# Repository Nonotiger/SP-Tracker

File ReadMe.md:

This project is about a Solar Panel which tracks the sun. The main focus for the project electrically, is the development of the BMS, and charger for the batteries. Code wise the main focus is the control of stepper motors, and the development of an algorithm for solar tracking based on energy output. Mechanically the focus is to develop stepper motor gears that can bear heavy loads, and to build a structure that can withstand Danish weather conditions.

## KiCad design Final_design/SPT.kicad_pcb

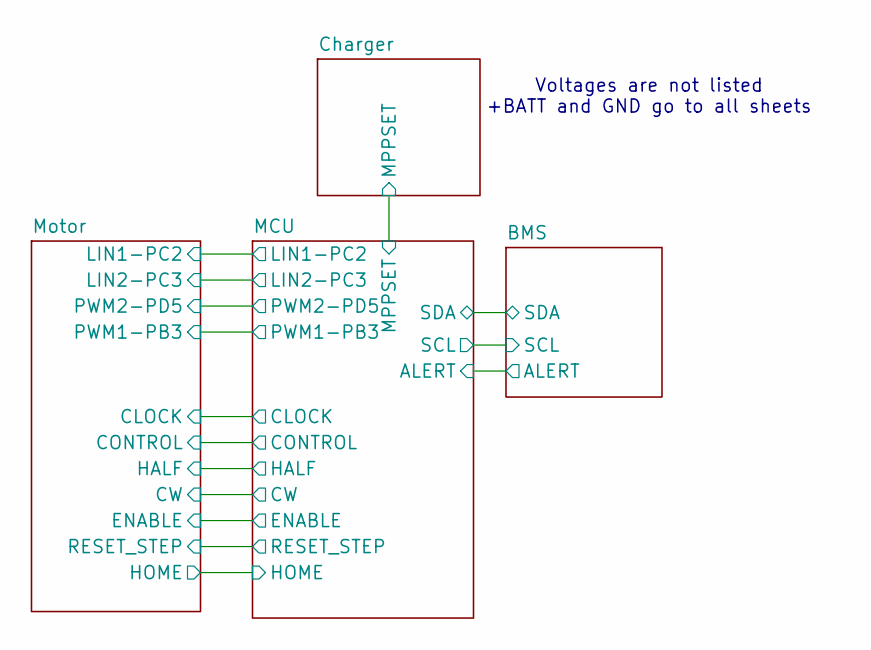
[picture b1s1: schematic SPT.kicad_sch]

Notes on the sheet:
Voltages are not listed +BATT and GND go to all sheets

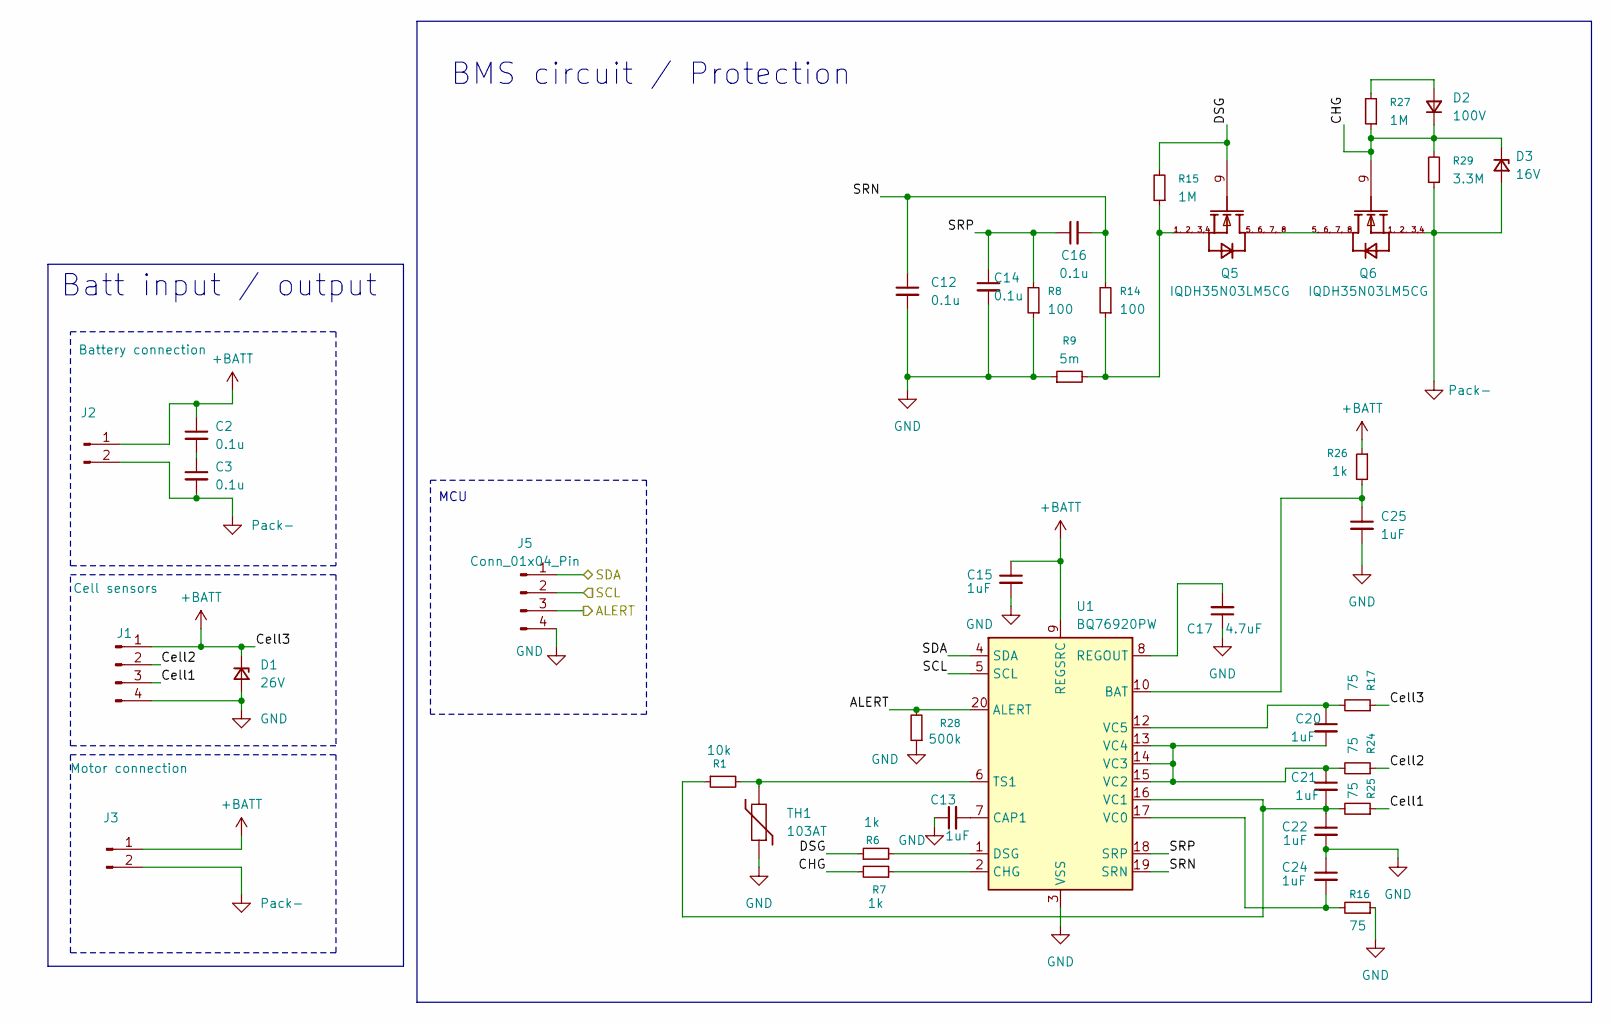
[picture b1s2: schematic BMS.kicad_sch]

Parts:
C2, C3, C12, C14, C16: 0.1u; C_0805_2012Metric_Pad1.18x1.45mm_HandSolder
C13, C15, C20, C21, C22, C24, C25: 1uF; C_0805_2012Metric_Pad1.18x1.45mm_HandSolder
C17: 4.7uF; C_0805_2012Metric_Pad1.18x1.45mm_HandSolder
D1: 26V; D_SOD-123
D2: 100V; D_SOD-123
D3: 16V; D_SOD-123
J1: Cell sensors; PinHeader_1x04_P2.54mm_Vertical
J2: Battery connection; TerminalBlock_Phoenix_MKDS-1,5-2_1x02_P5.00mm_Horizontal
J3: Motor connection; TerminalBlock_Phoenix_MKDS-1,5-2_1x02_P5.00mm_Horizontal
J5: Conn_01x04_Pin; PinHeader_1x04_P2.54mm_Vertical
Q5, Q6: IQDH35N03LM5CG; IFX-PG-TTFN-9-2-V
R1: 10k; R_0805_2012Metric_Pad1.20x1.40mm_HandSolder
R6, R7, R26: 1k; R_0805_2012Metric_Pad1.20x1.40mm_HandSolder
R8, R14: 100; R_0805_2012Metric_Pad1.20x1.40mm_HandSolder
R9: 5m; R_2512_6332Metric_Pad1.40x3.35mm_HandSolder
R15, R27: 1M; R_0805_2012Metric_Pad1.20x1.40mm_HandSolder
R16, R17, R24, R25: 75; R_0805_2012Metric_Pad1.20x1.40mm_HandSolder
R28: 500k; R_0805_2012Metric_Pad1.20x1.40mm_HandSolder
R29: 3.3M; R_0805_2012Metric_Pad1.20x1.40mm_HandSolder
TH1: 103AT; R_0603_1608Metric_Pad0.98x0.95mm_HandSolder
U1: BQ76920PW; TSSOP-20_4.4x6.5mm_P0.65mm

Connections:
+BATT: C2.1, C15.1, D1.1 (K), J1.1, J2.1, J3.1, R17.1, R26.1, U1.9 (REGSRC); also elsewhere on the board
/BMS/ALERT: J5.3, R28.2, U1.20 (ALERT); also elsewhere on the board
/BMS/CHG: D2.1 (K), D3.1 (K), Q6.9 (GATE), R7.2, R27.1, R29.2
/BMS/Cell1: J1.3, R25.1
/BMS/Cell2: J1.2, R24.1
/BMS/DSG: Q5.9 (GATE), R6.1, R15.2
/BMS/SCL: J5.2, U1.5 (SCL); also elsewhere on the board
/BMS/SDA: J5.1, U1.4 (SDA); also elsewhere on the board
/BMS/SRN: C12.1, C16.2, R14.2, U1.19 (SRN)
/BMS/SRP: C14.1, C16.1, R8.2, U1.18 (SRP)
GND: C12.2, C13.1, C14.2, C15.2, C17.1, C22.2, C24.1, C25.2, D1.2 (A), J1.4, J5.4, R8.1, R9.1, R16.1, R28.1, TH1.1, U1.3 (VSS); also elsewhere on the board
unnamed: C2.2, C3.1
unnamed: D2.2 (A), R27.2
unnamed: Q5.1 (SOURCE1), Q5.2 (SOURCE2), Q5.3 (SOURCE3), Q5.4 (SOURCE4), R9.2, R14.1, R15.1
unnamed: C25.1, R26.2, U1.10 (BAT)
unnamed: C13.2, U1.7 (CAP1)
unnamed: R7.1, U1.2 (CHG)
unnamed: R6.2, U1.1 (DSG)
unnamed: C17.2, U1.8 (REGOUT)
unnamed: R1.2, TH1.2, U1.6 (TS1)
unnamed: C24.2, R16.2, U1.17 (VC0)
unnamed: C21.2, C22.1, R1.1, R25.2, U1.16 (VC1)
unnamed: C20.2, C21.1, R24.2, U1.13 (VC4), U1.14 (VC3), U1.15 (VC2)
unnamed: C20.1, R17.2, U1.12 (VC5)
Pack-: C3.2, D3.2 (A), J2.2, J3.2, Q6.1 (SOURCE1), Q6.2 (SOURCE2), Q6.3 (SOURCE3), Q6.4 (SOURCE4), R29.1; also elsewhere on the board

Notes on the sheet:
Batt input / output
BMS circuit / Protection
MCU

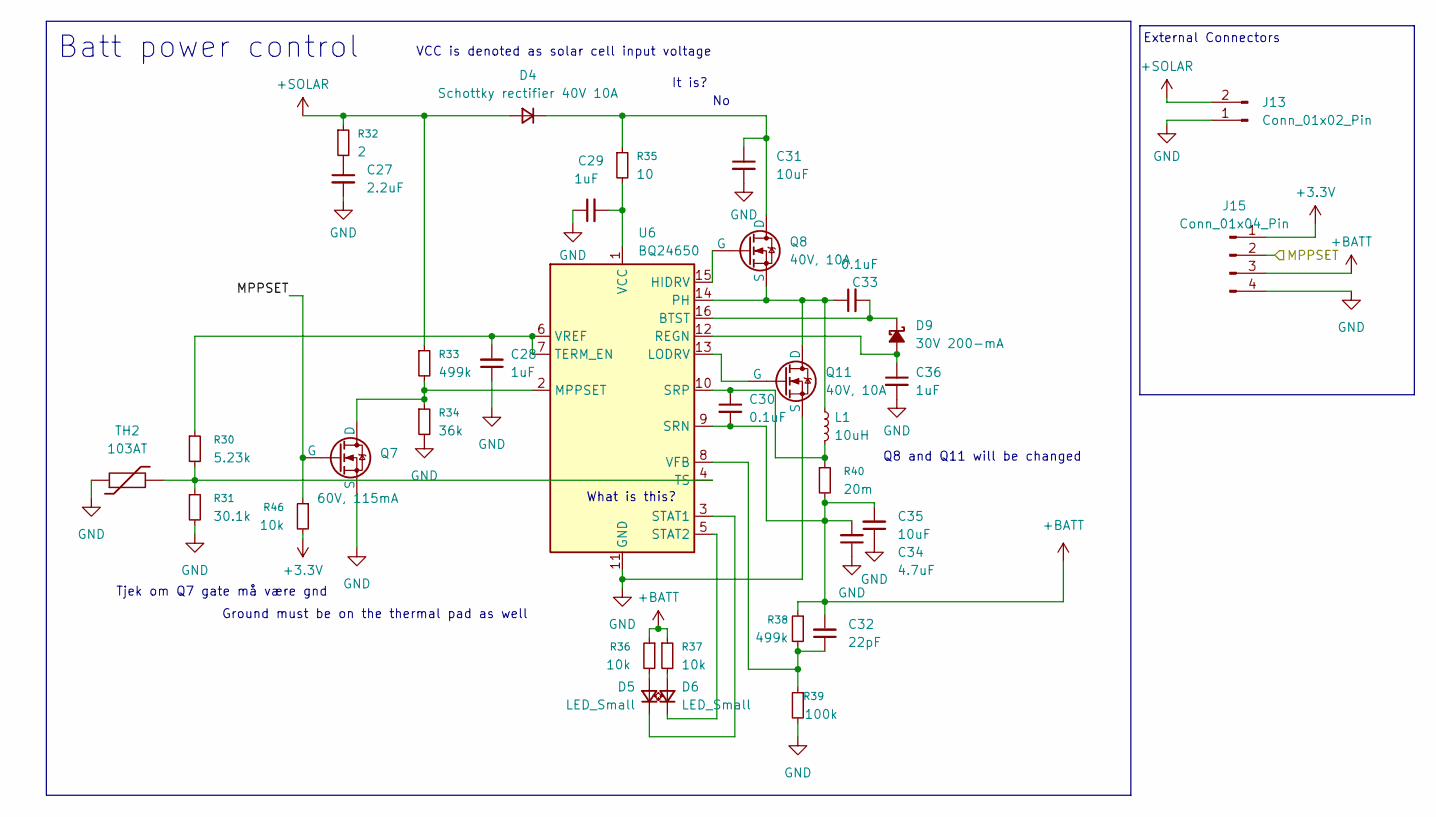
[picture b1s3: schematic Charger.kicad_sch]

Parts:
C27: 2.2uF; C_1210_3225Metric_Pad1.33x2.70mm_HandSolder
C28, C29, C36: 1uF; C_0805_2012Metric_Pad1.18x1.45mm_HandSolder
C30, C33: 0.1uF; C_0805_2012Metric_Pad1.18x1.45mm_HandSolder
C31, C35: 10uF; C_1210_3225Metric_Pad1.33x2.70mm_HandSolder
C32: 22pF; C_0805_2012Metric_Pad1.18x1.45mm_HandSolder
C34: 4.7uF; C_1210_3225Metric_Pad1.33x2.70mm_HandSolder
D4: Schottky rectifier 40V 10A; D_PowerDI-5
D5, D6: LED_Small; LED_0805_2012Metric_Pad1.15x1.40mm_HandSolder
D9: 30V 200-mA; SOT-23_Handsoldering
J13: Conn_01x02_Pin; TerminalBlock_Phoenix_MKDS-1,5-2_1x02_P5.00mm_Horizontal
J15: Conn_01x04_Pin; PinHeader_1x04_P2.54mm_Vertical
L1: 10uH; L_Vishay_IHLP-2525
Q7: 60V, 115mA; TO-220-3_Vertical
Q8, Q11: 40V, 10A; TO-220-3_Vertical
R30: 5.23k; R_0805_2012Metric_Pad1.20x1.40mm_HandSolder
R31: 30.1k; R_0805_2012Metric_Pad1.20x1.40mm_HandSolder
R32: 2; R_0805_2012Metric_Pad1.20x1.40mm_HandSolder
R33, R38: 499k; R_0805_2012Metric_Pad1.20x1.40mm_HandSolder
R34: 36k; R_0805_2012Metric_Pad1.20x1.40mm_HandSolder
R35: 10; R_0805_2012Metric_Pad1.20x1.40mm_HandSolder
R36, R37, R46: 10k; R_0805_2012Metric_Pad1.20x1.40mm_HandSolder
R39: 100k; R_0805_2012Metric_Pad1.20x1.40mm_HandSolder
R40: 20m; R_1206_3216Metric_Pad1.30x1.75mm_HandSolder
TH2: 103AT; R_0603_1608Metric_Pad0.98x0.95mm_HandSolder
U6: BQ24650; Texas_RVA_VQFN-16-1EP_3.5x3.5mm_P0.5mm_EP2.14x2.14mm_Therma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

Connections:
+3.3V: J15.1, R46.2; also elsewhere on the board
+BATT: C30.2, C32.2, C34.2, C35.2, J15.3, R36.1, R37.1, R38.1, R40.2, U6.9 (SRN); also elsewhere on the board
+SOLAR: D4.2 (A), J13.2, R32.1, R33.1
/Charger/MPPSET: J15.2, Q7.2 (G), R46.1; also elsewhere on the board
GND: C27.2, C28.1, C29.1, C31.2, C34.1, C35.1, C36.2, J13.1, J15.4, Q7.3 (S), Q11.3 (S), R31.2, R34.2, R39.2, TH2.1, U6.11 (GND), U6.17 (GND); also elsewhere on the board
unnamed: C27.1, R32.2
unnamed: C31.1, D4.1 (K), Q8.1 (D), R35.1
unnamed: D5.2 (A), R36.2
unnamed: D5.1 (K), U6.3 (STAT1)
unnamed: D6.2 (A), R37.2
unnamed: D6.1 (K), U6.5 (STAT2)
unnamed: C36.1, D9.2 (A), U6.12 (REGN)
unnamed: C33.2, D9.1 (K), U6.16 (BTST)
unnamed: Q7.1 (D), R33.2, R34.1, U6.2 (MPPSET)
unnamed: Q8.2 (G), U6.15 (HIDRV)
unnamed: C33.1, L1.1, Q8.3 (S), Q11.1 (D), U6.14 (PH)
unnamed: Q11.2 (G), U6.13 (LODRV)
unnamed: C30.1, L1.2, R40.1, U6.10 (SRP)
unnamed: C28.2, R30.1, U6.6 (VREF), U6.7 (TERM_EN)
unnamed: R30.2, R31.1, TH2.2, U6.4 (TS)
unnamed: C29.2, R35.2, U6.1 (VCC)
unnamed: C32.1, R38.2, R39.1, U6.8 (VFB)

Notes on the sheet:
Ground must be on the thermal pad as well
What is this?
External Connectors
Q8 and Q11 will be changed
VCC is denoted as solar cell input voltage
Tjek om Q7 gate må være gnd
Batt power control
It is?

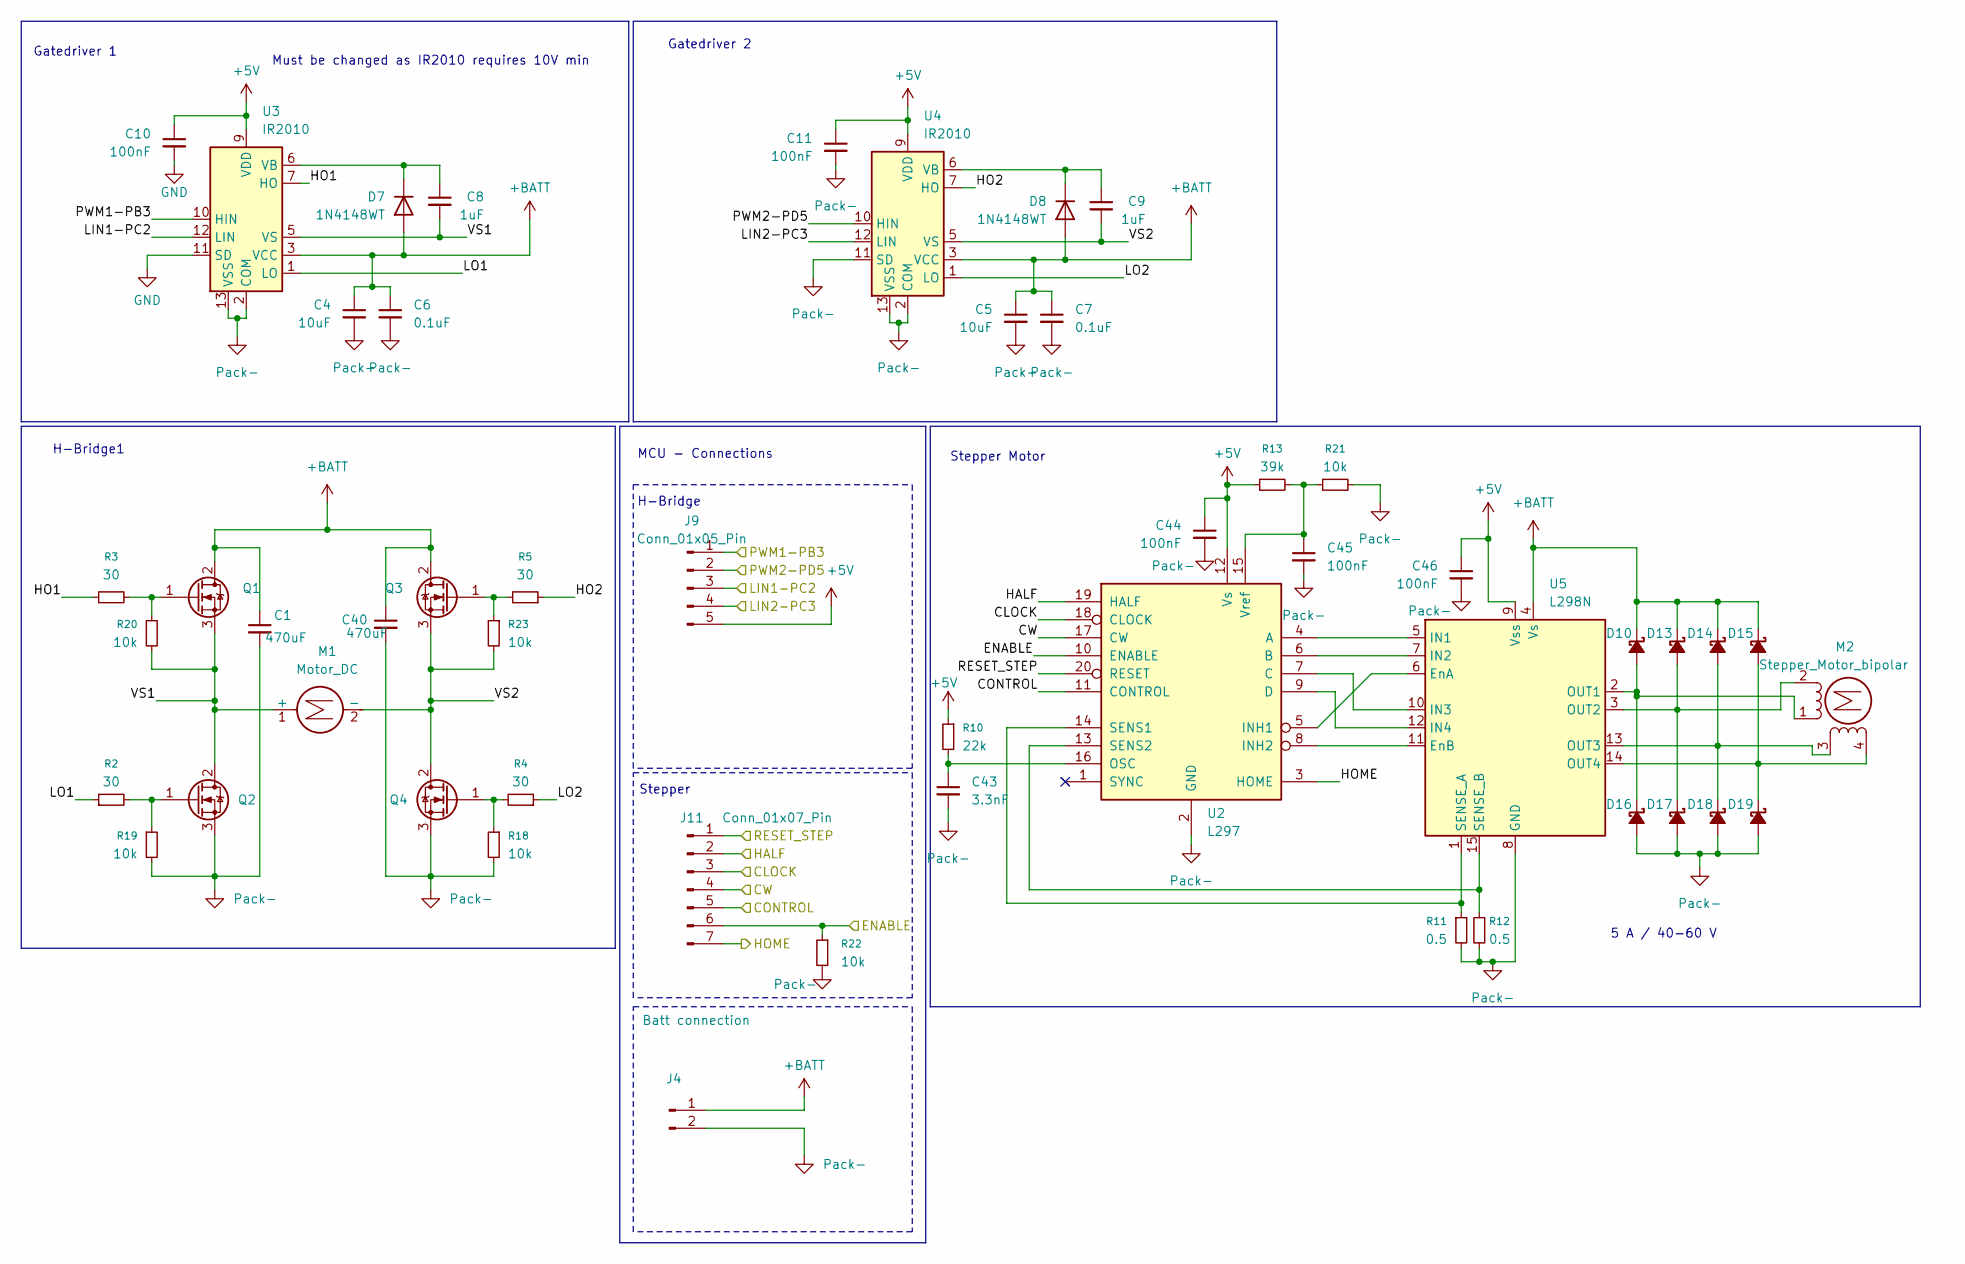
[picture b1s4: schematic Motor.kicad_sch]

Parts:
C1, C40: 470uF; CP_Radial_D12.5mm_P5.00mm
C4, C5: 10uF; C_1210_3225Metric_Pad1.33x2.70mm_HandSolder
C6, C7: 0.1uF; C_0805_2012Metric_Pad1.18x1.45mm_HandSolder
C8, C9: 1uF; C_0805_2012Metric_Pad1.18x1.45mm_HandSolder
C10, C11, C44, C45, C46: 100nF; C_0805_2012Metric_Pad1.18x1.45mm_HandSolder
C43: 3.3nF; C_0805_2012Metric_Pad1.18x1.45mm_HandSolder
D7, D8: 1N4148WT; D_SOD-523
D10, D13, D14, D15, D16, D17, D18, D19: D_Schottky_Small_Filled; D_SMA_Handsoldering
J4: Batt connection; TerminalBlock_Phoenix_MKDS-1,5-2_1x02_P5.00mm_Horizontal
J9: Conn_01x05_Pin; PinSocket_1x05_P2.54mm_Vertical
J11: Conn_01x07_Pin; PinHeader_1x07_P2.54mm_Vertical
M1: Motor_DC; TerminalBlock_Phoenix_MKDS-1,5-2_1x02_P5.00mm_Horizontal
M2: Stepper_Motor_bipolar; TerminalBlock_Phoenix_MKDS-1,5-4_1x04_P5.00mm_Horizontal
Q1, Q2, Q3, Q4: IRLZ34N; TO-220-3_Vertical
R2, R3, R4, R5: 30; R_0805_2012Metric_Pad1.20x1.40mm_HandSolder
R10: 22k; R_0805_2012Metric_Pad1.20x1.40mm_HandSolder
R11, R12: 0.5; R_0805_2012Metric_Pad1.20x1.40mm_HandSolder
R13: 39k; R_0805_2012Metric_Pad1.20x1.40mm_HandSolder
R18, R19, R20, R21, R22, R23: 10k; R_0805_2012Metric_Pad1.20x1.40mm_HandSolder
U2: L297; CERDIP-20_W7.62mm_SideBrazed
U3, U4: IR2010; DIP-14_W7.62mm
U5: L298N; TO-220-15_P2.54x5.08mm_StaggerOdd_Lead4.58mm_Vertical

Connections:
+5V: C10.1, C11.1, C44.1, C46.1, J9.5, R10.1, R13.1, U2.12 (Vs), U3.9 (VDD), U4.9 (VDD), U5.9 (Vss); also elsewhere on the board
+BATT: C1.1, C4.1, C5.1, C6.1, C7.1, C40.1, D7.2 (A), D8.2 (A), D10.1 (K), D13.1 (K), D14.1 (K), D15.1 (K), J4.1, Q1.2 (D), Q3.2 (D), U3.3 (VCC), U4.3 (VCC), U5.4 (Vs); also elsewhere on the board
/MCU/CLOCK: J11.3, U2.18 (CLOCK); also elsewhere on the board
/MCU/CONTROL: J11.5, U2.11 (CONTROL); also elsewhere on the board
/MCU/CW: J11.4, U2.17 (CW); also elsewhere on the board
/MCU/ENABLE: J11.6, R22.1, U2.10 (ENABLE); also elsewhere on the board
/MCU/HALF: J11.2, U2.19 (HALF); also elsewhere on the board
/MCU/HOME: J11.7, U2.3 (HOME); also elsewhere on the board
/MCU/LIN1-PC2: J9.3, U3.12 (LIN); also elsewhere on the board
/MCU/LIN2-PC3: J9.4, U4.12 (LIN); also elsewhere on the board
/MCU/PWM1-PB3: J9.1, U3.10 (HIN); also elsewhere on the board
/MCU/PWM2-PD5: J9.2, U4.10 (HIN); also elsewhere on the board
/MCU/RESET_STEP: J11.1, U2.20 (RESET); also elsewhere on the board
/Motor/HO1: R3.1, U3.7 (HO)
/Motor/HO2: R5.1, U4.7 (HO)
/Motor/LO1: R2.1, U3.1 (LO)
/Motor/LO2: R4.1, U4.1 (LO)
/Motor/VS1: C8.2, M1.1 (+), Q1.3 (S), Q2.2 (D), R20.2, U3.5 (VS)
/Motor/VS2: C9.2, M1.2 (-), Q3.3 (S), Q4.2 (D), R23.2, U4.5 (VS)
GND: C10.2, U3.11 (SD); also elsewhere on the board
unnamed: C8.1, D7.1 (K), U3.6 (VB)
unnamed: C9.1, D8.1 (K), U4.6 (VB)
unnamed: D10.2 (A), D16.1 (K), M2.1, U5.2 (OUT1)
unnamed: D13.2 (A), D17.1 (K), M2.2 (-_2), U5.3 (OUT2)
unnamed: D14.2 (A), D18.1 (K), M2.3, U5.13 (OUT3)
unnamed: D15.2 (A), D19.1 (K), M2.4, U5.14 (OUT4)
unnamed: Q1.1 (G), R3.2, R20.1
unnamed: Q2.1 (G), R2.2, R19.1
unnamed: Q3.1 (G), R5.2, R23.1
unnamed: Q4.1 (G), R4.2, R18.1
unnamed: U2.4 (A), U5.5 (IN1)
unnamed: U2.6 (B), U5.7 (IN2)
unnamed: U2.7 (C), U5.10 (IN3)
unnamed: U2.9 (D), U5.12 (IN4)
unnamed: U2.5 (INH1), U5.6 (EnA)
unnamed: U2.8 (INH2), U5.11 (EnB)
unnamed: C43.1, R10.2, U2.16 (OSC)
unnamed: R11.1, U2.14 (SENS1), U5.1 (SENSE_A)
unnamed: R12.1, U2.13 (SENS2), U5.15 (SENSE_B)
unnamed: C45.1, R13.2, R21.1, U2.15 (Vref)
Pack-: C1.2, C4.2, C5.2, C6.2, C7.2, C11.2, C40.2, C43.2, C44.2, C45.2, C46.2, D16.2 (A), D17.2 (A), D18.2 (A), D19.2 (A), J4.2, Q2.3 (S), Q4.3 (S), R11.2, R12.2, R18.2, R19.2, R21.2, R22.2, U2.2 (GND), U3.2 (COM), U3.13 (VSS), U4.2 (COM), U4.11 (SD), U4.13 (VSS), U5.8 (GND); also elsewhere on the board

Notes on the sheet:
Stepper
H-Bridge1
Stepper Motor
H-Bridge
Must be changed as IR2010 requires 10V min
Gatedriver 1
Gatedriver 2
MCU - Connections
5 A / 40-60 V

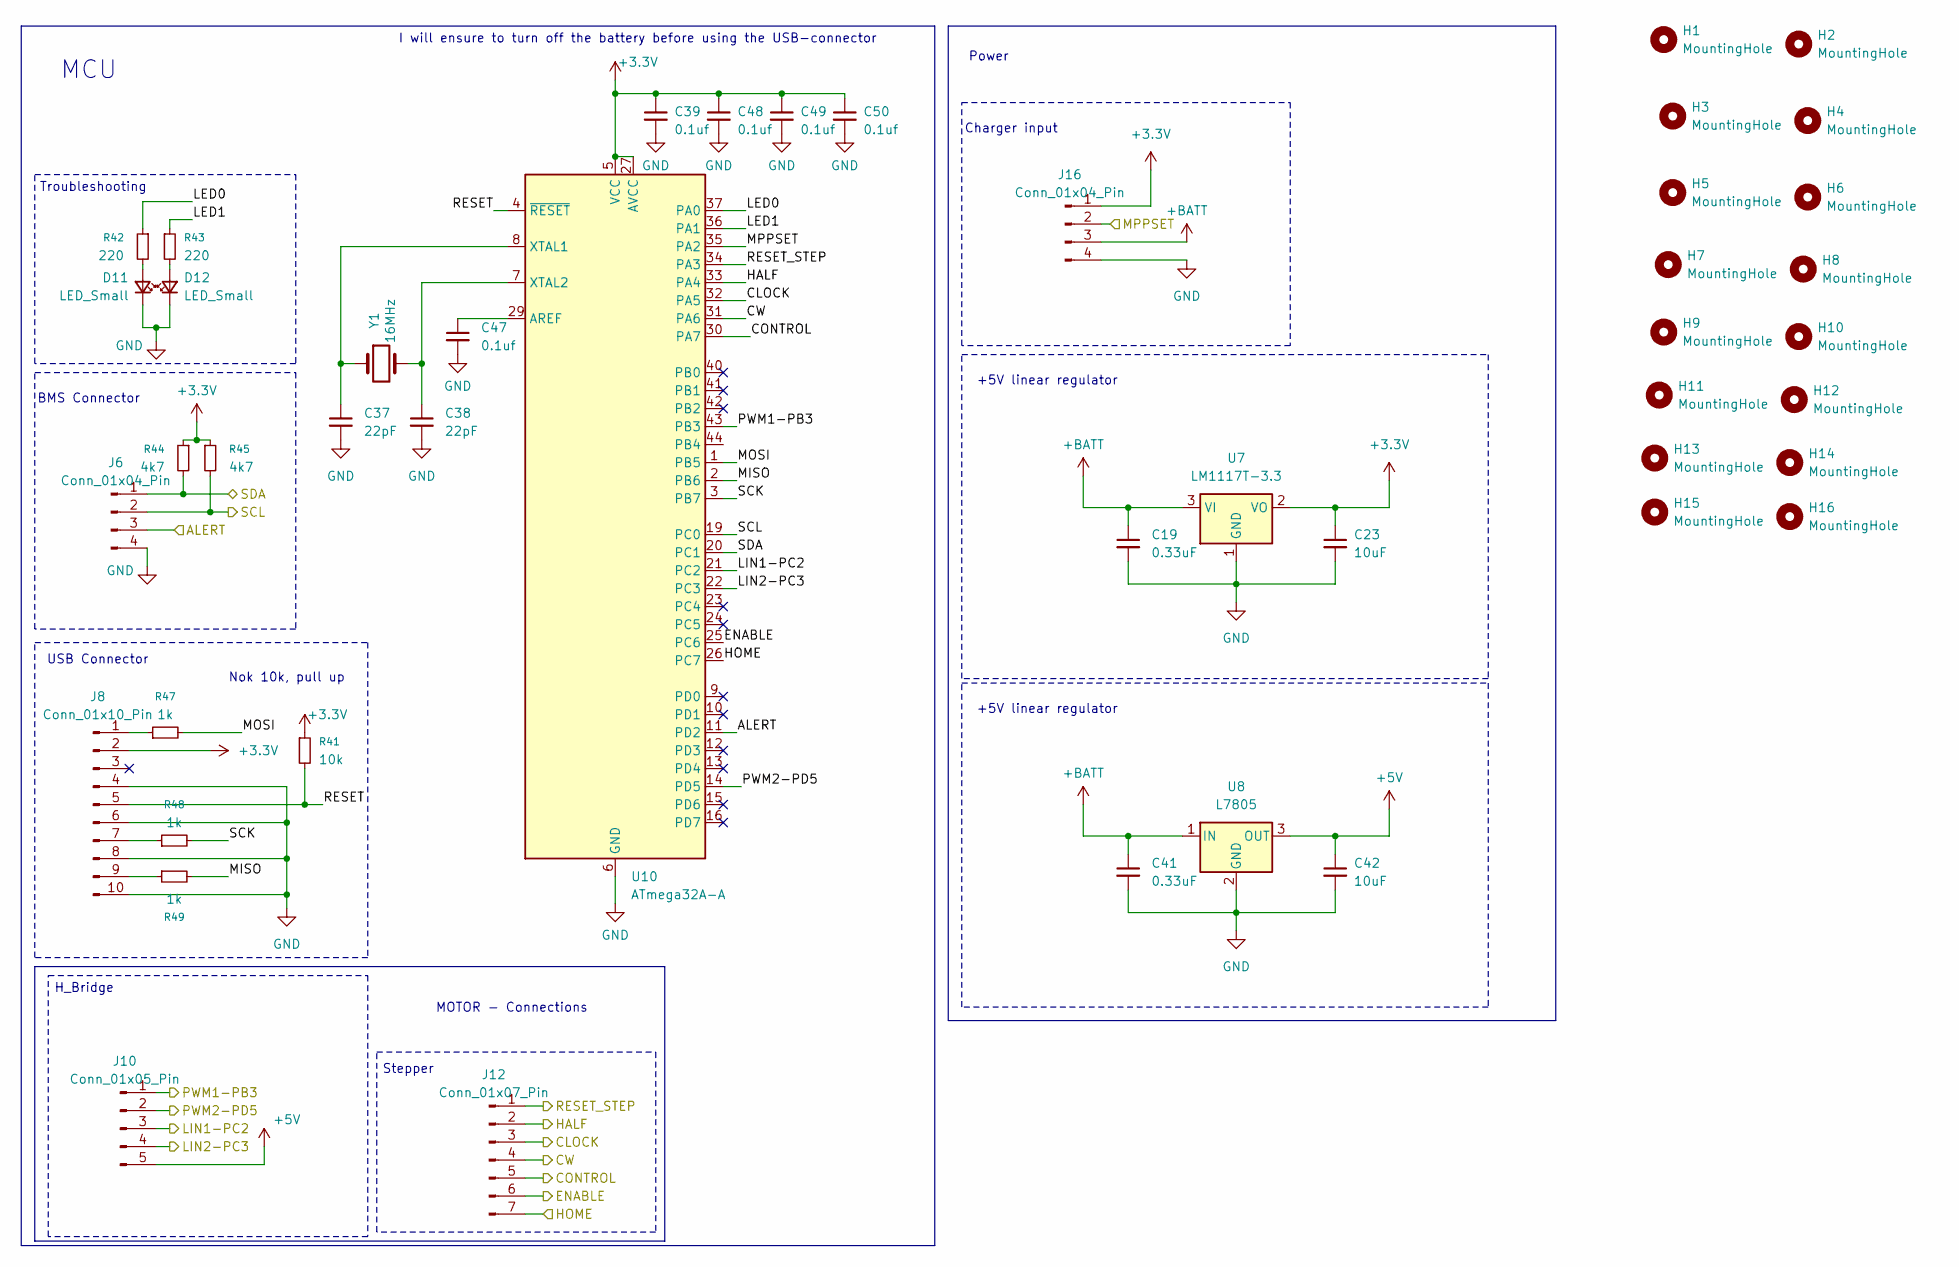
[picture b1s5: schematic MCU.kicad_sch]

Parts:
C19, C41: 0.33uF; C_0805_2012Metric_Pad1.18x1.45mm_HandSolder
C23, C42: 10uF; C_1206_3216Metric_Pad1.33x1.80mm_HandSolder
C37, C38: 22pF; C_0805_2012Metric_Pad1.18x1.45mm_HandSolder
C39, C47, C48, C49, C50: 0.1uf; C_0805_2012Metric_Pad1.18x1.45mm_HandSolder
D11, D12: LED_Small; LED_0805_2012Metric_Pad1.15x1.40mm_HandSolder
H1, H2, H3, H4, H5, H6, H7, H8, H9, H10, H11, H12, H13, H14, H15, H16: MountingHole
J6, J16: Conn_01x04_Pin; PinHeader_1x04_P2.54mm_Vertical
J8: Conn_01x10_Pin; PinHeader_2x05_P2.54mm_Vertical
J10: Conn_01x05_Pin; PinSocket_1x05_P2.54mm_Vertical
J12: Conn_01x07_Pin; PinHeader_1x07_P2.54mm_Vertical
R41: 10k; R_0805_2012Metric_Pad1.20x1.40mm_HandSolder
R42, R43: 220; R_0805_2012Metric_Pad1.20x1.40mm_HandSolder
R44, R45: 4k7; R_0805_2012Metric_Pad1.20x1.40mm_HandSolder
R47, R48, R49: 1k; R_0805_2012Metric_Pad1.20x1.40mm_HandSolder
U7: LM1117T-3.3; TO-220-3_Vertical
U8: L7805; TO-220-3_Vertical
U10: ATmega32A-A; TQFP-44_10x10mm_P0.8mm
Y1: 16MHz; Crystal_SMD_HC49-SD

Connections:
+3.3V: C23.1, C39.1, C48.1, C49.1, C50.1, J8.2, J16.1, R41.1, R44.1, R45.1, U7.2 (VO), U10.5 (VCC), U10.17 (VCC), U10.27 (AVCC), U10.38 (VCC); also elsewhere on the board
+5V: C42.1, J10.5, U8.3 (OUT); also elsewhere on the board
+BATT: C19.1, C41.1, J16.3, U7.3 (VI), U8.1 (IN); also elsewhere on the board
/BMS/ALERT: J6.3, U10.11 (PD2); also elsewhere on the board
/BMS/SCL: J6.2, R45.2, U10.19 (PC0); also elsewhere on the board
/BMS/SDA: J6.1, R44.2, U10.20 (PC1); also elsewhere on the board
/Charger/MPPSET: J16.2, U10.35 (PA2); also elsewhere on the board
/MCU/CLOCK: J12.3, U10.32 (PA5); also elsewhere on the board
/MCU/CONTROL: J12.5, U10.30 (PA7); also elsewhere on the board
/MCU/CW: J12.4, U10.31 (PA6); also elsewhere on the board
/MCU/ENABLE: J12.6, U10.25 (PC6); also elsewhere on the board
/MCU/HALF: J12.2, U10.33 (PA4); also elsewhere on the board
/MCU/HOME: J12.7, U10.26 (PC7); also elsewhere on the board
/MCU/LED0: R42.1, U10.37 (PA0)
/MCU/LED1: R43.1, U10.36 (PA1)
/MCU/LIN1-PC2: J10.3, U10.21 (PC2); also elsewhere on the board
/MCU/LIN2-PC3: J10.4, U10.22 (PC3); also elsewhere on the board
/MCU/MISO: R49.2, U10.2 (PB6)
/MCU/MOSI: R47.2, U10.1 (PB5)
/MCU/PWM1-PB3: J10.1, U10.43 (PB3); also elsewhere on the board
/MCU/PWM2-PD5: J10.2, U10.14 (PD5); also elsewhere on the board
/MCU/RESET: J8.5, R41.2, U10.4 (~RESET)
/MCU/RESET_STEP: J12.1, U10.34 (PA3); also elsewhere on the board
/MCU/SCK: R48.2, U10.3 (PB7)
GND: C19.2, C23.2, C37.2, C38.2, C39.2, C41.2, C42.2, C47.2, C48.2, C49.2, C50.2, D11.1 (K), D12.1 (K), J6.4, J8.4, J8.6, J8.8, J8.10, J16.4, U7.1 (GND), U8.2 (GND), U10.6 (GND), U10.18 (GND), U10.28 (GND), U10.39 (GND); also elsewhere on the board
unnamed: D11.2 (A), R42.2
unnamed: D12.2 (A), R43.2
unnamed: J8.1, R47.1
unnamed: J8.7, R48.1
unnamed: J8.9, R49.1
unnamed: C47.1, U10.29 (AREF)
unnamed: C37.1, U10.8 (XTAL1), Y1.1
unnamed: C38.1, U10.7 (XTAL2), Y1.2

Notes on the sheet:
USB Connector
MOTOR - Connections
Stepper
I will ensure to turn off the battery before using the USB-connector
MCU
Power
+5V linear regulator
BMS Connector
Troubleshooting
H_Bridge
Charger input
Nok 10k, pull up

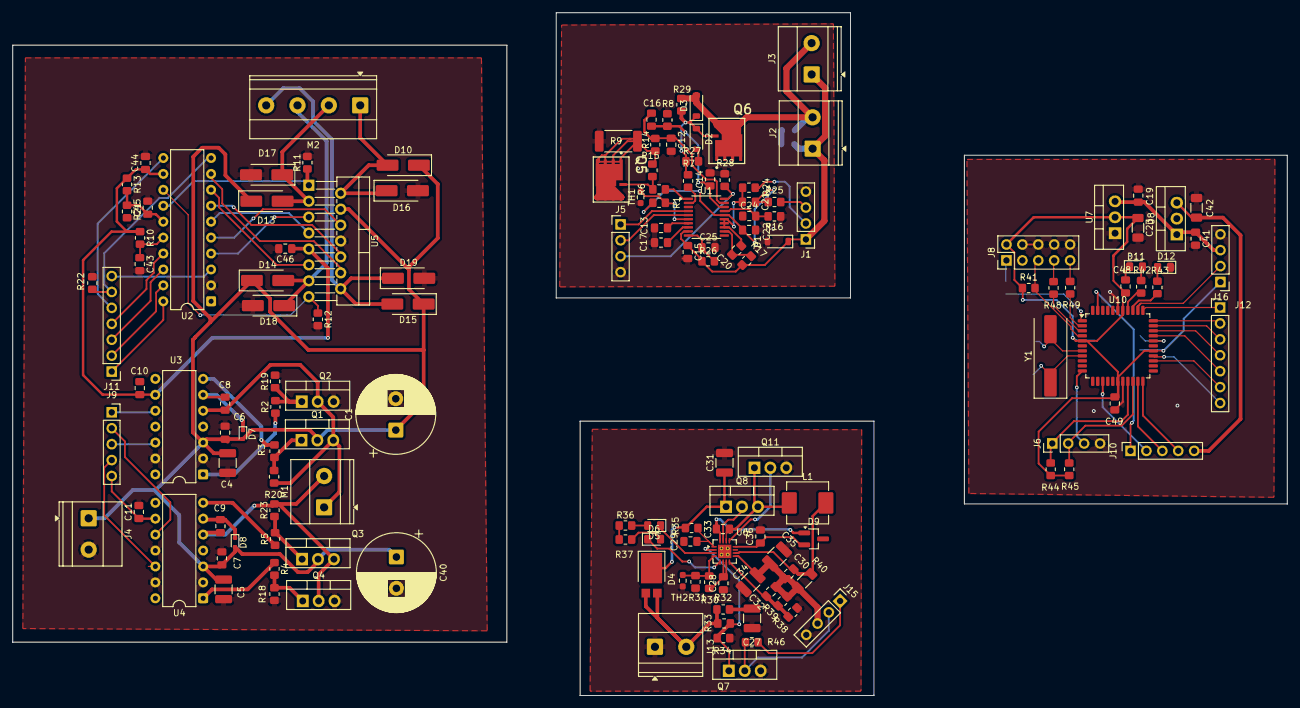
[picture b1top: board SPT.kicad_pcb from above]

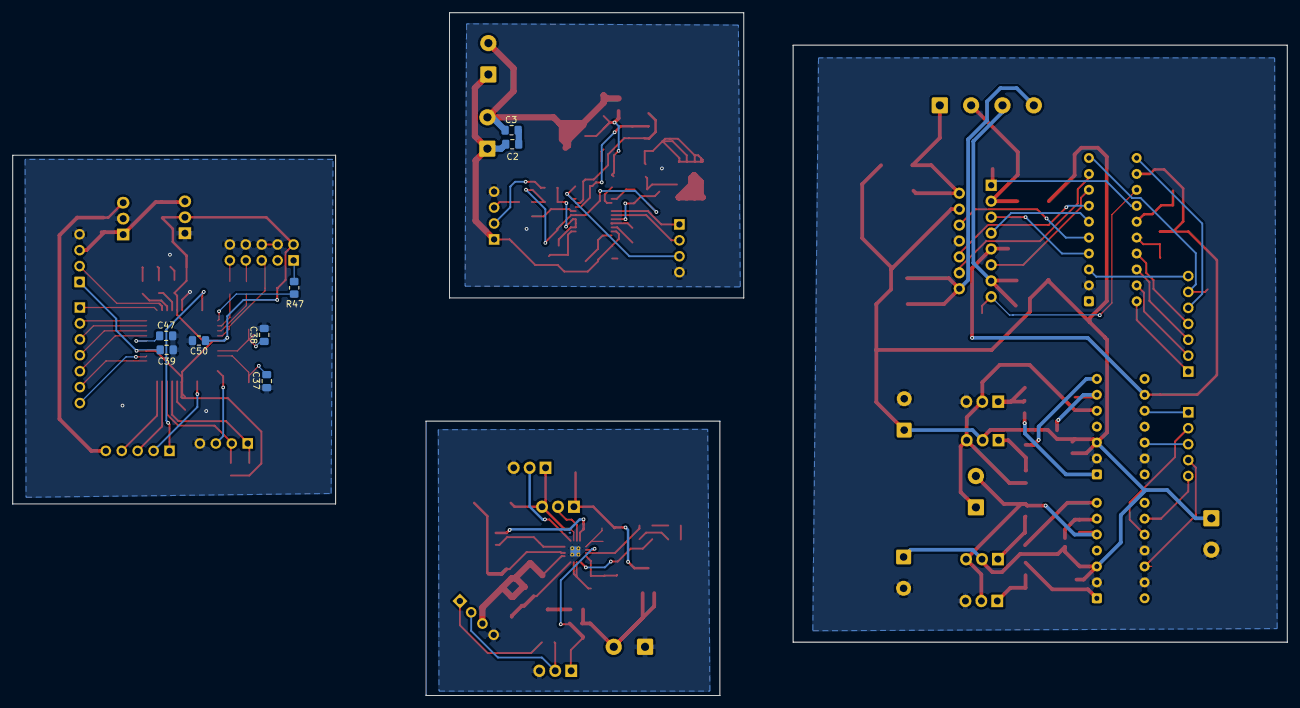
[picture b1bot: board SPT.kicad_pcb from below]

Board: 2 copper layers, 203.3 x 108.9 mm, 154 parts (8 on the bottom side), 97 nets.

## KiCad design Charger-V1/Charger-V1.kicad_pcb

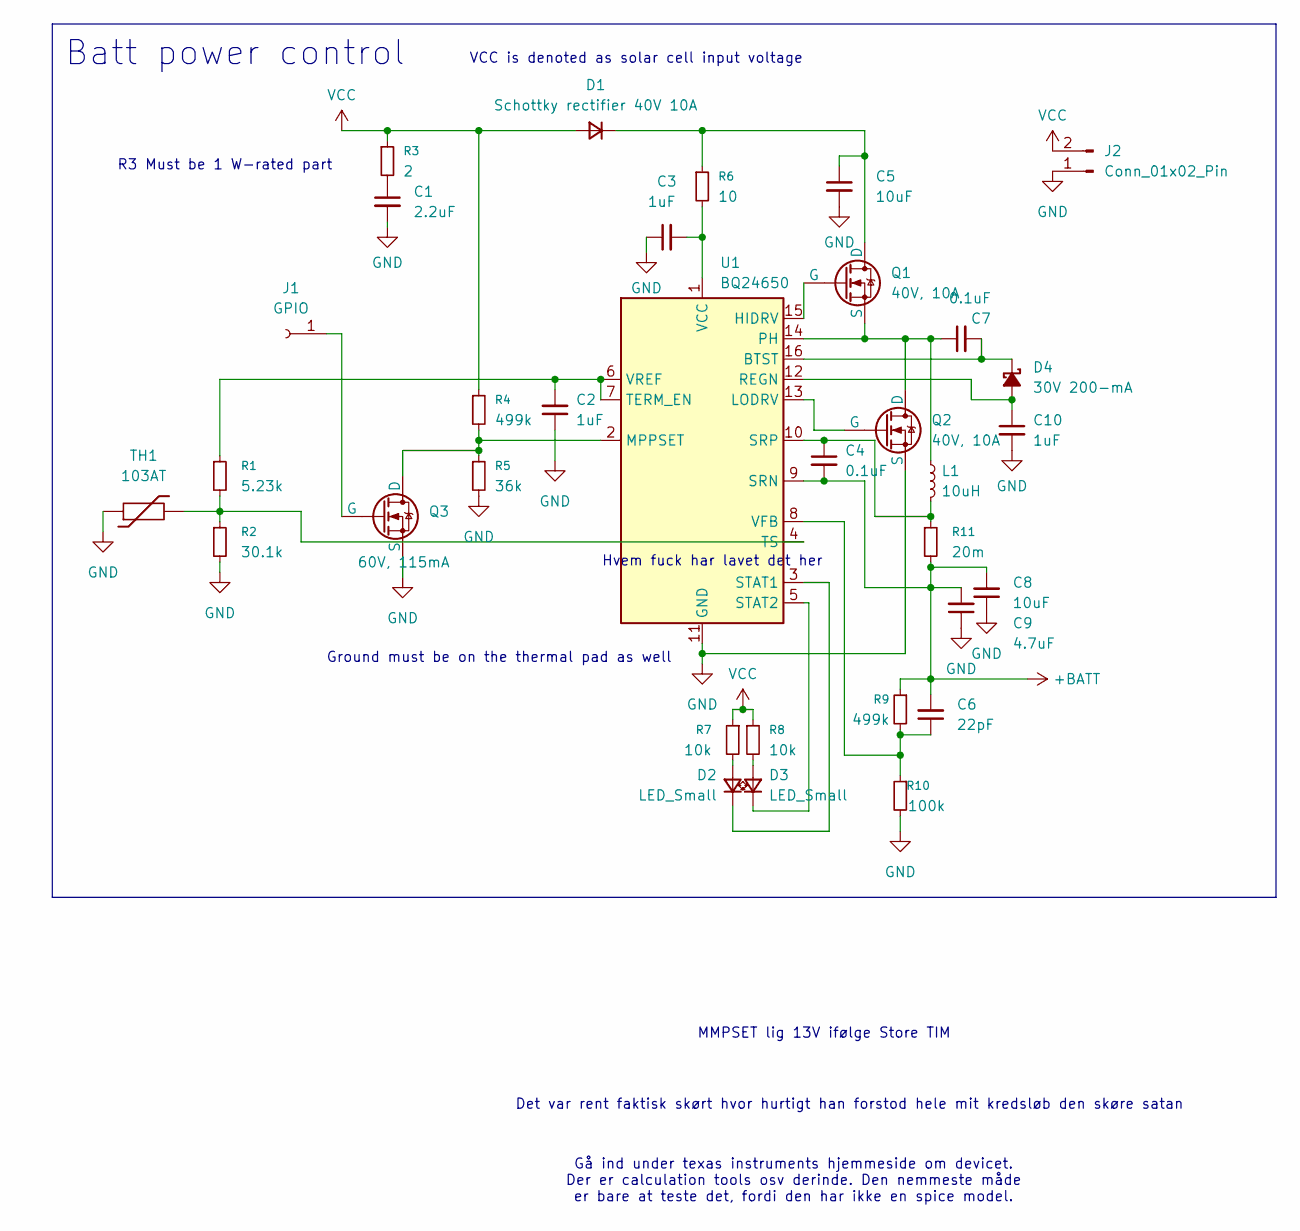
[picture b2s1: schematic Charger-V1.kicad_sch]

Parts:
C1: 2.2uF; C_1210_3225Metric_Pad1.33x2.70mm_HandSolder
C2, C3, C10: 1uF; C_0805_2012Metric_Pad1.18x1.45mm_HandSolder
C4, C7: 0.1uF; C_0805_2012Metric_Pad1.18x1.45mm_HandSolder
C5, C8: 10uF; C_1210_3225Metric_Pad1.33x2.70mm_HandSolder
C6: 22pF; C_0603_1608Metric_Pad1.08x0.95mm_HandSolder
C9: 4.7uF; C_1210_3225Metric_Pad1.33x2.70mm_HandSolder
D1: Schottky rectifier 40V 10A; D_PowerDI-5
D2, D3: LED_Small; D_0603_1608Metric
D4: 30V 200-mA; SOT-23
J1: GPIO; PinHeader_1x01_P2.54mm_Horizontal
J2: Conn_01x02_Pin; TerminalBlock_Phoenix_MKDS-1,5-2-5.08_1x02_P5.08mm_Horizont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
L1: 10uH; L_Vishay_IHLP-2525
Q1, Q2: 40V, 10A; PowerPAK_SO-8_Dual
Q3: 60V, 115mA; SOT-23
R1: 5.23k; R_0805_2012Metric_Pad1.20x1.40mm_HandSolder
R2: 30.1k; R_0805_2012Metric_Pad1.20x1.40mm_HandSolder
R3: 2; R_0805_2012Metric_Pad1.20x1.40mm_HandSolder
R4, R9: 499k; R_0805_2012Metric_Pad1.20x1.40mm_HandSolder
R5: 36k; R_0805_2012Metric_Pad1.20x1.40mm_HandSolder
R6: 10; R_0805_2012Metric_Pad1.20x1.40mm_HandSolder
R7, R8: 10k; R_0805_2012Metric_Pad1.20x1.40mm_HandSolder
R10: 100k; R_0805_2012Metric_Pad1.20x1.40mm_HandSolder
R11: 20m; R_1206_3216Metric_Pad1.30x1.75mm_HandSolder
TH1: 103AT; R_0805_2012Metric_Pad1.20x1.40mm_HandSolder
U1: BQ24650; Texas_RVA_VQFN-16-1EP_3.5x3.5mm_P0.5mm_EP2.14x2.14mm_Therma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

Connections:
+BATT: C4.2, C6.2, C8.2, C9.2, R9.1, R11.2, U1.9 (SRN)
GND: C1.2, C2.1, C3.1, C5.2, C8.1, C9.1, C10.2, J2.1, Q2.3 (S), Q3.3 (S), R2.2, R5.2, R10.2, TH1.1, U1.11 (GND), U1.17 (GND)
unnamed: C1.1, R3.2
unnamed: C5.1, D1.1 (K), Q1.1 (D), R6.1
unnamed: D2.2 (A), R7.2
unnamed: D2.1 (K), U1.3 (STAT1)
unnamed: D3.2 (A), R8.2
unnamed: D3.1 (K), U1.5 (STAT2)
unnamed: C10.1, D4.2 (A), U1.12 (REGN)
unnamed: C7.2, D4.1 (K), U1.16 (BTST)
unnamed: J1.1 (Pin_1_1), Q3.2 (G)
unnamed: Q1.2 (G), U1.15 (HIDRV)
unnamed: C7.1, L1.1, Q1.3 (S), Q2.1 (D), U1.14 (PH)
unnamed: Q2.2 (G), U1.13 (LODRV)
unnamed: Q3.1 (D), R4.2, R5.1, U1.2 (MPPSET)
unnamed: C4.1, L1.2, R11.1, U1.10 (SRP)
unnamed: C2.2, R1.1, U1.6 (VREF), U1.7 (TERM_EN)
unnamed: R1.2, R2.1, TH1.2, U1.4 (TS)
unnamed: C3.2, R6.2, U1.1 (VCC)
unnamed: C6.1, R9.2, R10.1, U1.8 (VFB)
VCC: D1.2 (A), J2.2, R3.1, R4.1, R7.1, R8.1

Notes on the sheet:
Hvem fuck har lavet det her
Gå ind under texas instruments hjemmeside om devicet. Der er calculation tools osv derinde. Den nemmeste måde er bare at teste det, fordi den har ikke en spice model.
Det var rent faktisk skørt hvor hurtigt han forstod hele mit kredsløb den skøre satan
MMPSET lig 13V ifølge Store TIM
Batt power control
VCC is denoted as solar cell input voltage
Ground must be on the thermal pad as well
R3 Must be 1 W-rated part

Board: 2 copper layers, 33 parts (0 on the bottom side), 21 nets, no tracks yet.
